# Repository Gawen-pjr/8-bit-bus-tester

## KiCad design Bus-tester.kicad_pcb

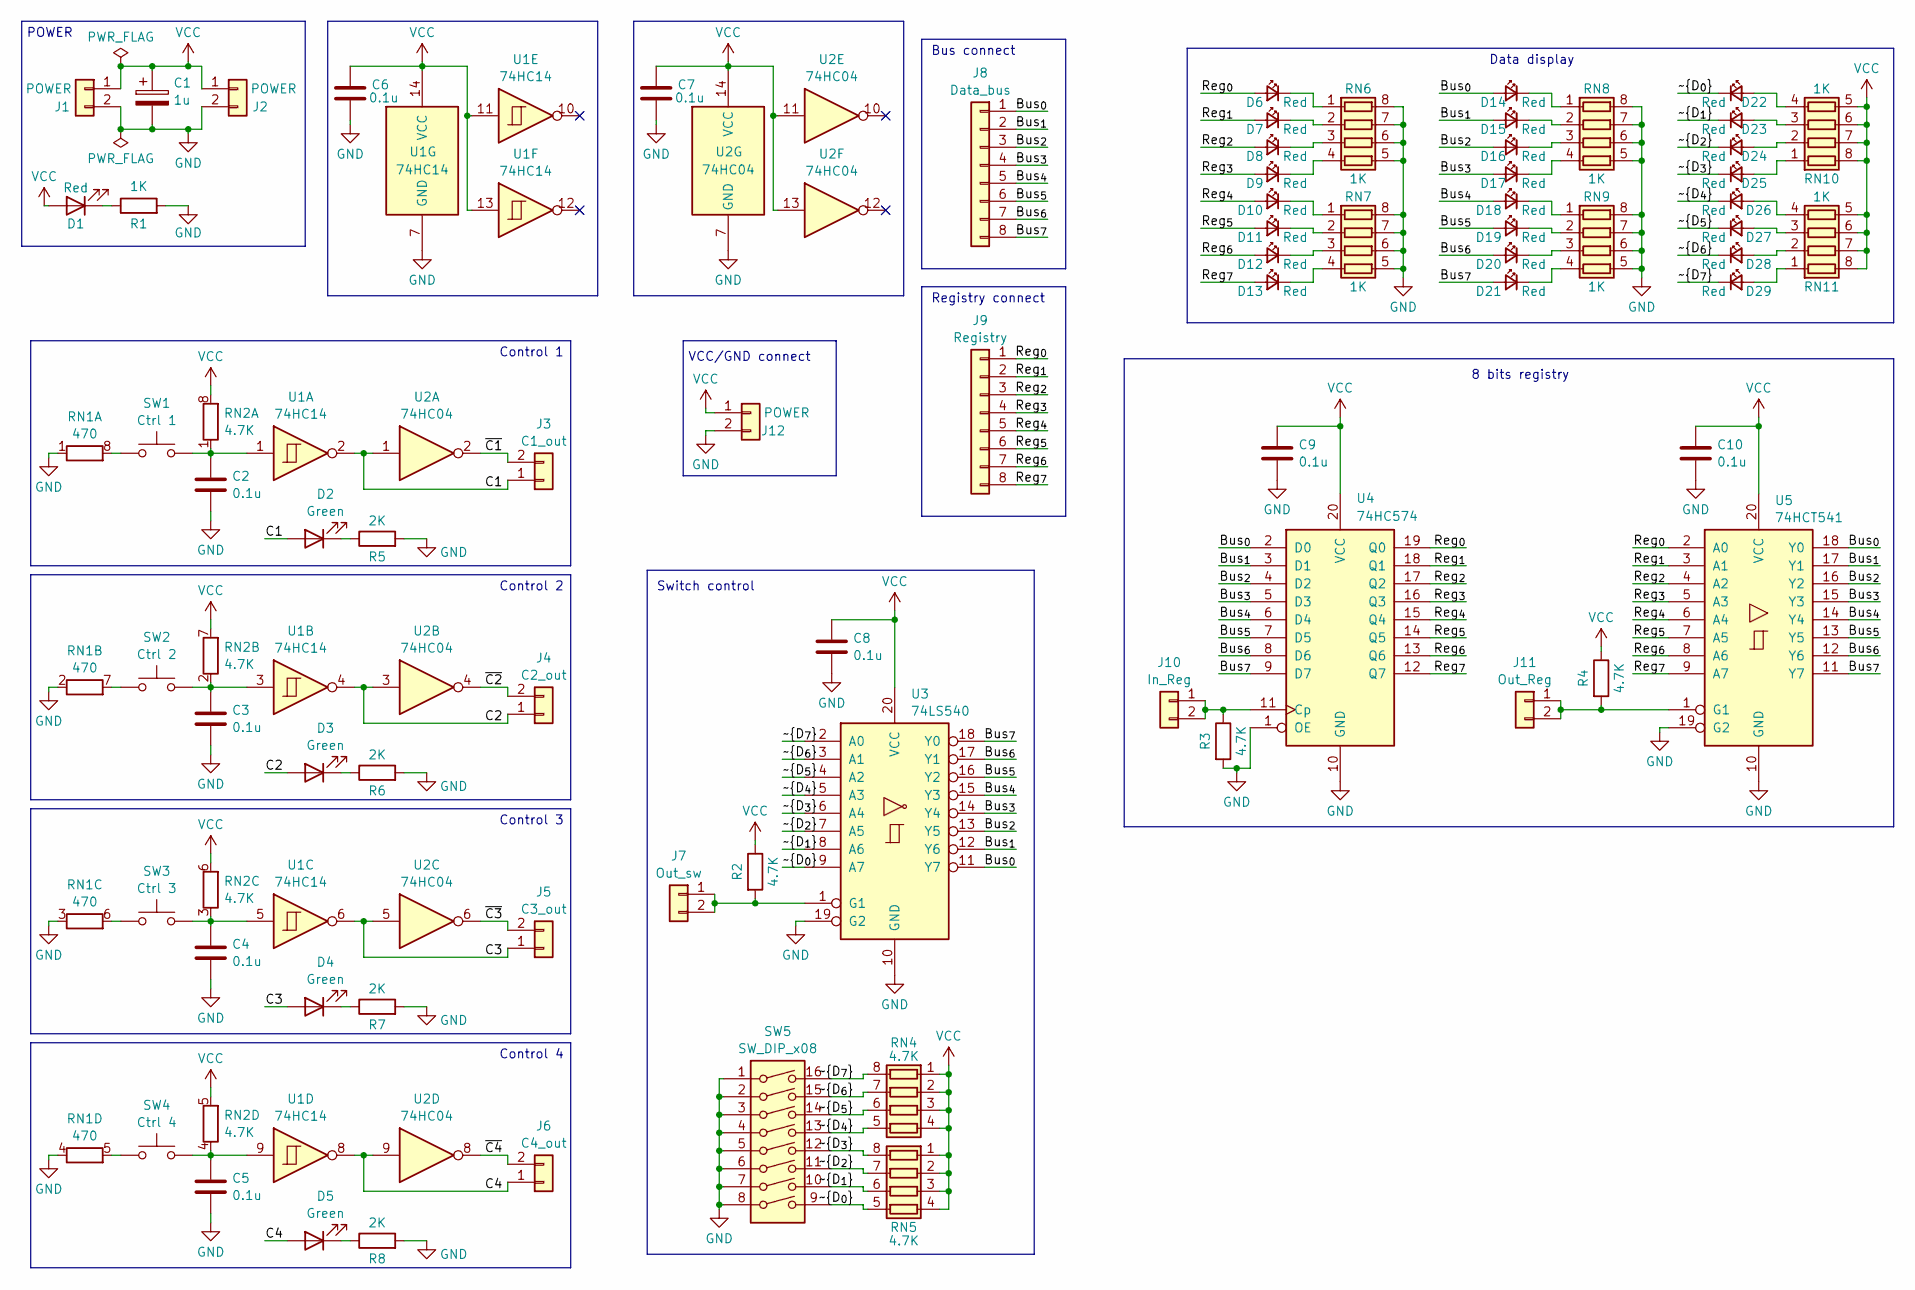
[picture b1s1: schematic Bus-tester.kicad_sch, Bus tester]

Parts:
C1: 1u; CP_Radial_D5.0mm_P2.50mm
C2, C3, C4, C5, C6, C7, C8, C9, C10: 0.1u; C_1206_3216Metric
D1, D6, D7, D8, D9, D10, D11, D12, D13, D14, D15, D16, D17, D18, D19, D20, D21, D22, D23, D24, D25, D26, D27, D28, D29: Red; LED_1206_3216Metric
D2, D3, D4, D5: Green; LED_1206_3216Metric
J1, J2, J12: POWER; PinSocket_1x02_P2.54mm_Vertical
J3: C1_out; PinSocket_1x02_P2.54mm_Vertical
J4: C2_out; PinSocket_1x02_P2.54mm_Vertical
J5: C3_out; PinSocket_1x02_P2.54mm_Vertical
J6: C4_out; PinSocket_1x02_P2.54mm_Vertical
J7: Out_sw; PinSocket_1x02_P2.54mm_Vertical
J8: Data_bus; PinSocket_1x08_P2.54mm_Vertical
J9: Registry; PinSocket_1x08_P2.54mm_Vertical
J10: In_Reg; PinSocket_1x02_P2.54mm_Vertical
J11: Out_Reg; PinSocket_1x02_P2.54mm_Vertical
R1: 1K; R_1206_3216Metric
R2, R3, R4: 4.7K; R_1206_3216Metric
R5, R6, R7, R8: 2K; R_1206_3216Metric
RN1: 470; R_Array_Convex_4x0603
RN2, RN4, RN5: 4.7K; R_Array_Convex_4x0603
RN6, RN7, RN8, RN9, RN10, RN11: 1K; R_Array_Convex_4x0603
SW1: Ctrl 1; SW_PUSH_6mm_H5mm
SW2: Ctrl 2; SW_PUSH_6mm_H5mm
SW3: Ctrl 3; SW_PUSH_6mm_H5mm
SW4: Ctrl 4; SW_PUSH_6mm_H5mm
SW5: SW_DIP_x08; SW_DIP_SPSTx08_Slide_9.78x22.5mm_W7.62mm_P2.54mm
U1: 74HC14; SOIC-14_3.9x8.7mm_P1.27mm
U2: 74HC04; SOIC-14_3.9x8.7mm_P1.27mm
U3: 74LS540; SOIC-20W_7.5x12.8mm_P1.27mm
U4: 74HC574; SOIC-20W_7.5x12.8mm_P1.27mm
U5: 74HCT541; SOIC-20W_7.5x12.8mm_P1.27mm

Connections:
/Bus_{0}: D14.2 (A), J8.1, U3.11 (Y7), U4.2 (D0), U5.18 (Y0)
/Bus_{1}: D15.2 (A), J8.2, U3.12 (Y6), U4.3 (D1), U5.17 (Y1)
/Bus_{2}: D16.2 (A), J8.3, U3.13 (Y5), U4.4 (D2), U5.16 (Y2)
/Bus_{3}: D17.2 (A), J8.4, U3.14 (Y4), U4.5 (D3), U5.15 (Y3)
/Bus_{4}: D18.2 (A), J8.5, U3.15 (Y3), U4.6 (D4), U5.14 (Y4)
/Bus_{5}: D19.2 (A), J8.6, U3.16 (Y2), U4.7 (D5), U5.13 (Y5)
/Bus_{6}: D20.2 (A), J8.7, U3.17 (Y1), U4.8 (D6), U5.12 (Y6)
/Bus_{7}: D21.2 (A), J8.8, U3.18 (Y0), U4.9 (D7), U5.11 (Y7)
/C1: D2.2 (A), J3.1, U1.2, U2.1
/C2: D3.2 (A), J4.1, U1.4, U2.3
/C3: D4.2 (A), J5.1, U1.6, U2.5
/C4: D5.2 (A), J6.1, U1.8, U2.9
/Reg_{0}: D6.2 (A), J9.1, U4.19 (Q0), U5.2 (A0)
/Reg_{1}: D7.2 (A), J9.2, U4.18 (Q1), U5.3 (A1)
/Reg_{2}: D8.2 (A), J9.3, U4.17 (Q2), U5.4 (A2)
/Reg_{3}: D9.2 (A), J9.4, U4.16 (Q3), U5.5 (A3)
/Reg_{4}: D10.2 (A), J9.5, U4.15 (Q4), U5.6 (A4)
/Reg_{5}: D11.2 (A), J9.6, U4.14 (Q5), U5.7 (A5)
/Reg_{6}: D12.2 (A), J9.7, U4.13 (Q6), U5.8 (A6)
/Reg_{7}: D13.2 (A), J9.8, U4.12 (Q7), U5.9 (A7)
/~C1: J3.2, U2.2
/~C2: J4.2, U2.4
/~C3: J5.2, U2.6
/~C4: J6.2, U2.8
/~D_{0}: D22.1 (K), RN5.5 (R4.2), SW5.9, U3.9 (A7)
/~D_{1}: D23.1 (K), RN5.6 (R3.2), SW5.10, U3.8 (A6)
/~D_{2}: D24.1 (K), RN5.7 (R2.2), SW5.11, U3.7 (A5)
/~D_{3}: D25.1 (K), RN5.8 (R1.2), SW5.12, U3.6 (A4)
/~D_{4}: D26.1 (K), RN4.5 (R4.2), SW5.13, U3.5 (A3)
/~D_{5}: D27.1 (K), RN4.6 (R3.2), SW5.14, U3.4 (A2)
/~D_{6}: D28.1 (K), RN4.7 (R2.2), SW5.15, U3.3 (A1)
/~D_{7}: D29.1 (K), RN4.8 (R1.2), SW5.16, U3.2 (A0)
GND: C1.2, C2.2, C3.2, C4.2, C5.2, C6.2, C7.2, C8.2, C9.2, C10.2, J1.2, J2.2, J12.2, R1.2, R3.2, R5.2, R6.2, R7.2, R8.2, RN1.1 (R1.1), RN1.2 (R2.1), RN1.3 (R3.1), RN1.4 (R4.1), RN6.5 (R4.2), RN6.6 (R3.2), RN6.7 (R2.2), RN6.8 (R1.2), RN7.5 (R4.2), RN7.6 (R3.2), RN7.7 (R2.2), RN7.8 (R1.2), RN8.5 (R4.2), RN8.6 (R3.2), RN8.7 (R2.2), RN8.8 (R1.2), RN9.5 (R4.2), RN9.6 (R3.2), RN9.7 (R2.2), RN9.8 (R1.2), SW5.1, SW5.2, SW5.3, SW5.4, SW5.5, SW5.6, SW5.7, SW5.8, U1.7 (GND), U2.7 (GND), U3.10 (GND), U3.19 (G2), U4.1 (OE), U4.10 (GND), U5.10 (GND), U5.19 (G2)
unnamed: D1.1 (K), R1.1
unnamed: D2.1 (K), R5.1
unnamed: D3.1 (K), R6.1
unnamed: D4.1 (K), R7.1
unnamed: D5.1 (K), R8.1
unnamed: D6.1 (K), RN6.1 (R1.1)
unnamed: D7.1 (K), RN6.2 (R2.1)
unnamed: D8.1 (K), RN6.3 (R3.1)
unnamed: D9.1 (K), RN6.4 (R4.1)
unnamed: D10.1 (K), RN7.1 (R1.1)
unnamed: D11.1 (K), RN7.2 (R2.1)
unnamed: D12.1 (K), RN7.3 (R3.1)
unnamed: D13.1 (K), RN7.4 (R4.1)
unnamed: D14.1 (K), RN8.1 (R1.1)
unnamed: D15.1 (K), RN8.2 (R2.1)
unnamed: D16.1 (K), RN8.3 (R3.1)
unnamed: D17.1 (K), RN8.4 (R4.1)
unnamed: D18.1 (K), RN9.1 (R1.1)
unnamed: D19.1 (K), RN9.2 (R2.1)
unnamed: D20.1 (K), RN9.3 (R3.1)
unnamed: D21.1 (K), RN9.4 (R4.1)
unnamed: D22.2 (A), RN10.4 (R4.1)
unnamed: D23.2 (A), RN10.3 (R3.1)
unnamed: D24.2 (A), RN10.2 (R2.1)
unnamed: D25.2 (A), RN10.1 (R1.1)
unnamed: D26.2 (A), RN11.4 (R4.1)
unnamed: D27.2 (A), RN11.3 (R3.1)
unnamed: D28.2 (A), RN11.2 (R2.1)
unnamed: D29.2 (A), RN11.1 (R1.1)
unnamed: J7.1, J7.2, R2.2, U3.1 (G1)
unnamed: J10.1, J10.2, R3.1, U4.11 (Cp)
unnamed: J11.1, J11.2, R4.2, U5.1 (G1)
unnamed: RN1.8 (R1.2), SW1.1
unnamed: RN1.7 (R2.2), SW2.1
unnamed: RN1.6 (R3.2), SW3.1
unnamed: RN1.5 (R4.2), SW4.1
unnamed: C2.1, RN2.1 (R1.1), SW1.2, U1.1
unnamed: C3.1, RN2.2 (R2.1), SW2.2, U1.3
unnamed: C4.1, RN2.3 (R3.1), SW3.2, U1.5
unnamed: C5.1, RN2.4 (R4.1), SW4.2, U1.9
VCC: C1.1, C6.1, C7.1, C8.1, C9.1, C10.1, D1.2 (A), J1.1, J2.1, J12.1, R2.1, R4.1, RN2.5 (R4.2), RN2.6 (R3.2), RN2.7 (R2.2), RN2.8 (R1.2), RN4.1 (R1.1), RN4.2 (R2.1), RN4.3 (R3.1), RN4.4 (R4.1), RN5.1 (R1.1), RN5.2 (R2.1), RN5.3 (R3.1), RN5.4 (R4.1), RN10.5 (R4.2), RN10.6 (R3.2), RN10.7 (R2.2), RN10.8 (R1.2), RN11.5 (R4.2), RN11.6 (R3.2), RN11.7 (R2.2), RN11.8 (R1.2), U1.11, U1.13, U1.14 (VCC), U2.11, U2.13, U2.14 (VCC), U3.20 (VCC), U4.20 (VCC), U5.20 (VCC)

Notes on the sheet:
Control 1
Switch control
Registry connect
Bus connect
Data display
8 bits registry
Control 4
VCC/GND connect
Control 2
POWER
Control 3

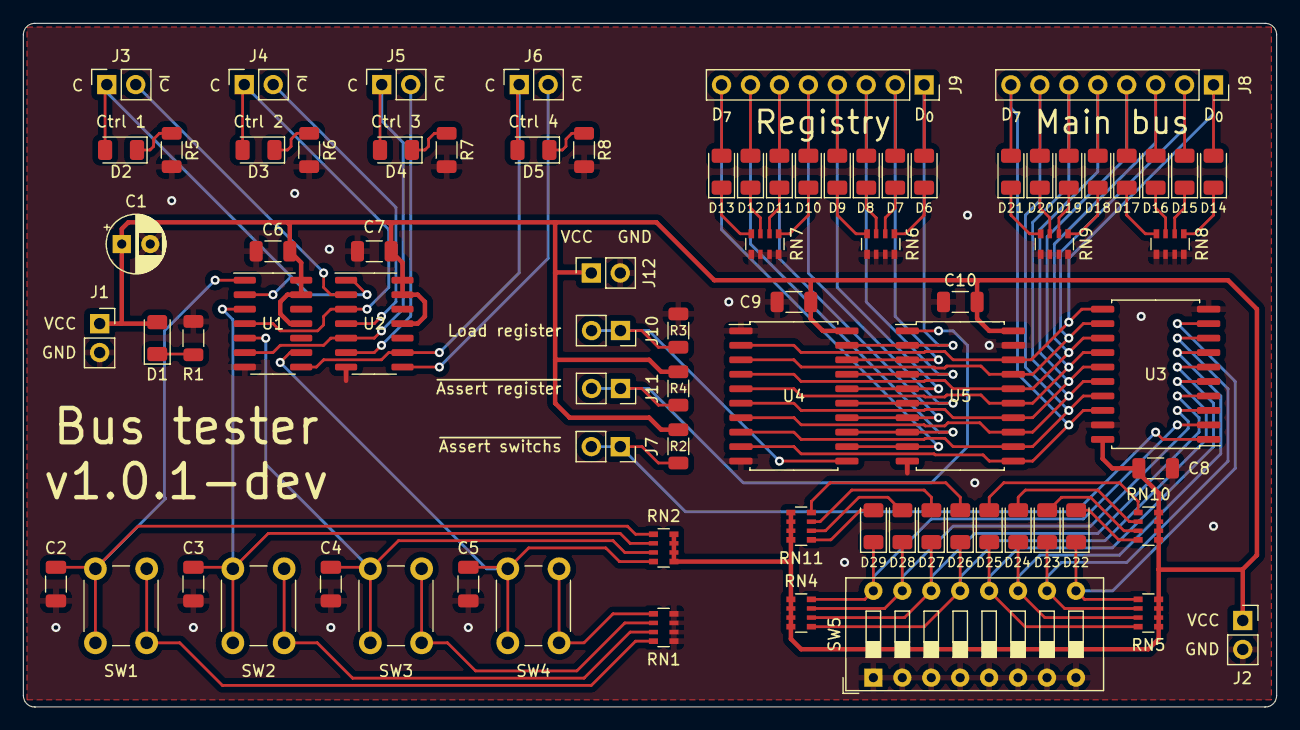
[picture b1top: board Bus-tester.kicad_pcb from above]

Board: 2 copper layers, 110.0 x 60.0 mm, 79 parts (0 on the bottom side), 74 nets.

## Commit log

2023-12-20 optimize routing for register chip
2023-12-20 optimize routing
2023-12-20 remove adhesive layer from gerber export
2023-12-21 make PCB marking parameterized
2023-12-21 prepare project for release
2023-12-26 change register chip ref for cleaner routing
2023-12-29 add rounded corners to PCB edge cuts
2023-12-29 change resistor arrays footprints
